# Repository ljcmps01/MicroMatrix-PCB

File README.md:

# MicroMatrix-PCB
PCB for the MicroMatrix project

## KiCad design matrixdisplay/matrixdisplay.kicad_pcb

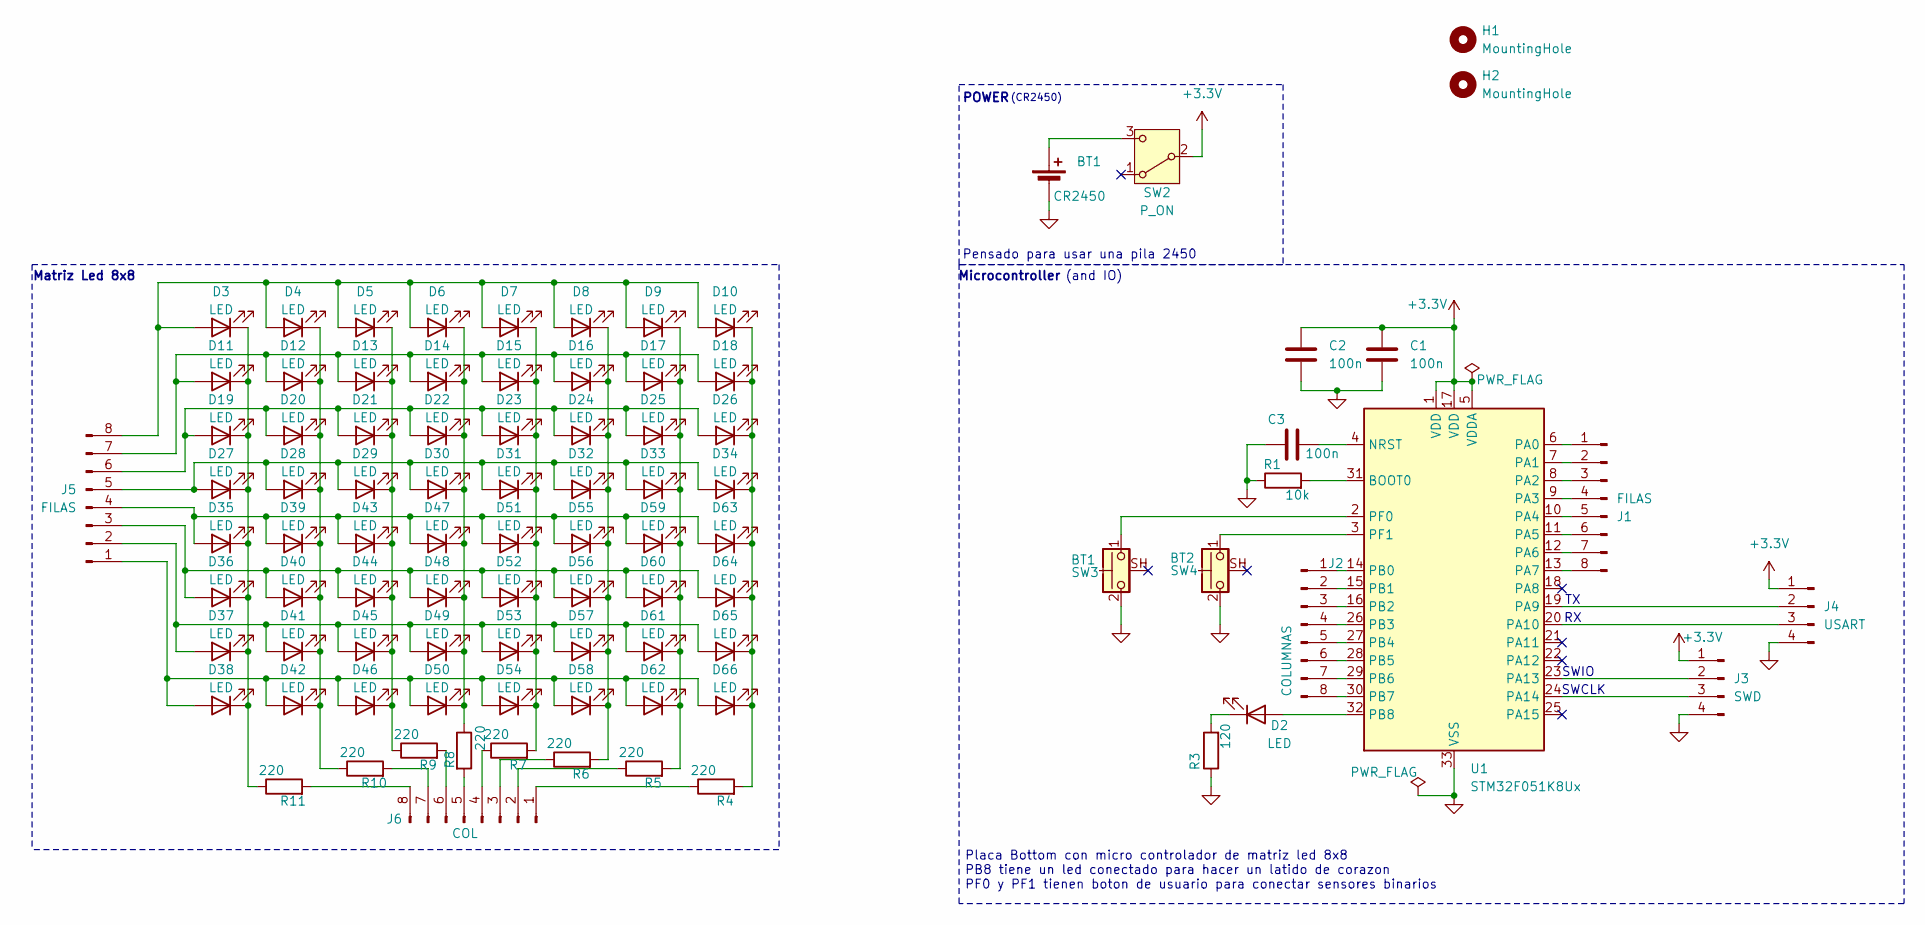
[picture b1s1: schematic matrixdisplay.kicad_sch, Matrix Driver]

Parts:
BT1: CR2450; BatteryHolder_ComfortableElectronic_CH273-2450_1x2450
C1, C2, C3: 100n; C_0603_1608Metric
D2, D3, D4, D5, D6, D7, D8, D9, D10, D11, D12, D13, D14, D15, D16, D17, D18, D19, D20, D21, D22, D23, D24, D25, D26, D27, D28, D29, D30, D31, D32, D33, D34, D35, D36, D37, D38, D39, D40, D41, D42, D43, D44, D45, D46, D47, D48, D49, D50, D51, D52, D53, D54, D55, D56, D57, D58, D59, D60, D61, D62, D63, D64, D65, D66: LED; LED_0603_1608Metric; Manufacturer Part # BL-HJC36G-AV-TRB
H1, H2: MountingHole; MountingHole_2mm
J1: FILAS; PinSocket_1x08_P2.54mm_Vertical
J2: COLUMNAS; PinSocket_1x08_P2.54mm_Vertical
J3: SWD; PinHeader_1x04_P2.54mm_Vertical
J4: USART; PinHeader_1x04_P2.54mm_Vertical
J5: FILAS; PinHeader_1x08_P2.54mm_Vertical
J6: COL; PinHeader_1x08_P2.54mm_Vertical
R1: 10k; R_0603_1608Metric
R3: 120; R_0603_1608Metric
R4, R5, R6, R7, R8, R9, R10, R11: 220; R_0402_1005Metric
SW2: P_ON; SW_SPDT_PCM12; Manufacturer Part # MSK12C02
SW3: BT1; TS24CA; Manufacturer Part # TS24CAC393942
SW4: BT2; TS24CA; Manufacturer Part # TS24CAC393942
U1: STM32F051K8Ux; QFN-32-1EP_5x5mm_P0.5mm_EP3.45x3.45mm

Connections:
+3.3V: C1.1, C2.1, J3.1, J4.1, SW2.2 (B), U1.1 (VDD), U1.5 (VDDA), U1.17 (VDD)
GND: BT1.2 (-), C1.2, C2.2, C3.2, J3.4, J4.4, R1.1, R3.1, SW3.2, SW4.2, U1.33 (VSS); also elsewhere on the board
unnamed 2: BT1.1 (+), SW2.3 (C); also elsewhere on the board
unnamed: D2.2 (A), U1.32 (PB8)
unnamed: D2.1 (K), R3.2
unnamed: D3.2 (A), D4.2 (A), D5.2 (A), D6.2 (A), D7.2 (A), D8.2 (A), D9.2 (A), D10.2 (A), J5.8
unnamed: D10.1 (K), D18.1 (K), D26.1 (K), D34.1 (K), D63.1 (K), D64.1 (K), D65.1 (K), D66.1 (K), R4.2
unnamed: D11.2 (A), D12.2 (A), D13.2 (A), D14.2 (A), D15.2 (A), D16.2 (A), D17.2 (A), D18.2 (A), J5.7
unnamed: D3.1 (K), D11.1 (K), D19.1 (K), D27.1 (K), D35.1 (K), D36.1 (K), D37.1 (K), D38.1 (K), R11.1
unnamed: D4.1 (K), D12.1 (K), D20.1 (K), D28.1 (K), D39.1 (K), D40.1 (K), D41.1 (K), D42.1 (K), R10.1
unnamed: D5.1 (K), D13.1 (K), D21.1 (K), D29.1 (K), D43.1 (K), D44.1 (K), D45.1 (K), D46.1 (K), R9.1
unnamed: D6.1 (K), D14.1 (K), D22.1 (K), D30.1 (K), D47.1 (K), D48.1 (K), D49.1 (K), D50.1 (K), R8.1
unnamed: D7.1 (K), D15.1 (K), D23.1 (K), D31.1 (K), D51.1 (K), D52.1 (K), D53.1 (K), D54.1 (K), R7.2
unnamed: D8.1 (K), D16.1 (K), D24.1 (K), D32.1 (K), D55.1 (K), D56.1 (K), D57.1 (K), D58.1 (K), R6.2
unnamed: D9.1 (K), D17.1 (K), D25.1 (K), D33.1 (K), D59.1 (K), D60.1 (K), D61.1 (K), D62.1 (K), R5.2
unnamed: D19.2 (A), D20.2 (A), D21.2 (A), D22.2 (A), D23.2 (A), D24.2 (A), D25.2 (A), D26.2 (A), J5.6
unnamed: D27.2 (A), D28.2 (A), D29.2 (A), D30.2 (A), D31.2 (A), D32.2 (A), D33.2 (A), D34.2 (A), J5.5
unnamed: D35.2 (A), D39.2 (A), D43.2 (A), D47.2 (A), D51.2 (A), D55.2 (A), D59.2 (A), D63.2 (A), J5.4
unnamed: D36.2 (A), D40.2 (A), D44.2 (A), D48.2 (A), D52.2 (A), D56.2 (A), D60.2 (A), D64.2 (A), J5.3
unnamed: D37.2 (A), D41.2 (A), D45.2 (A), D49.2 (A), D53.2 (A), D57.2 (A), D61.2 (A), D65.2 (A), J5.2
unnamed: D38.2 (A), D42.2 (A), D46.2 (A), D50.2 (A), D54.2 (A), D58.2 (A), D62.2 (A), D66.2 (A), J5.1
unnamed: J1.1, U1.6 (PA0)
unnamed: J1.2, U1.7 (PA1)
unnamed: J1.3, U1.8 (PA2)
unnamed: J1.4, U1.9 (PA3)
unnamed: J1.5, U1.10 (PA4)
unnamed: J1.6, U1.11 (PA5)
unnamed: J1.7, U1.12 (PA6)
unnamed: J1.8, U1.13 (PA7)
unnamed: J2.1, U1.14 (PB0)
unnamed: J2.2, U1.15 (PB1)
unnamed: J2.3, U1.16 (PB2)
unnamed: J2.4, U1.26 (PB3)
unnamed: J2.5, U1.27 (PB4)
unnamed: J2.6, U1.28 (PB5)
unnamed: J2.7, U1.29 (PB6)
unnamed: J2.8, U1.30 (PB7)
unnamed: J3.2, U1.23 (PA13)
unnamed: J3.3, U1.24 (PA14)
unnamed: J4.2, U1.19 (PA9)
unnamed: J4.3, U1.20 (PA10)
unnamed: J6.1, R4.1
unnamed: J6.2, R5.1
unnamed: J6.3, R6.1
unnamed: J6.4, R7.1
unnamed: J6.5, R8.2
unnamed: J6.6, R9.2
unnamed: J6.7, R10.2
unnamed: J6.8, R11.2
unnamed: R1.2, U1.31 (BOOT0)
unnamed: C3.1, U1.4 (NRST)
unnamed: SW3.1, U1.2 (PF0)
unnamed: SW4.1, U1.3 (PF1)

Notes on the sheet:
(CR2450)
Placa Bottom con micro controlador de matriz led 8x8 PB8 tiene un led conectado para hacer un latido de corazon PF0 y PF1 tienen boton de usuario para conectar sensores binarios
SWIO
Microcontroller
(and IO)
Matriz Led 8x8
Pensado para usar una pila 2450
SWCLK
POWER

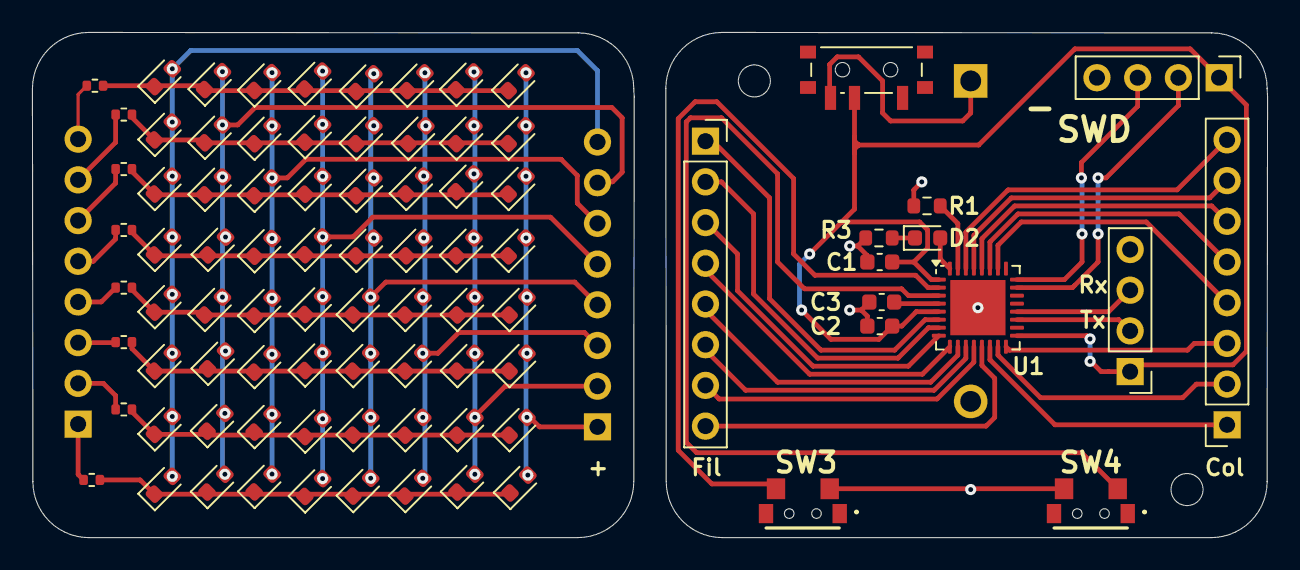
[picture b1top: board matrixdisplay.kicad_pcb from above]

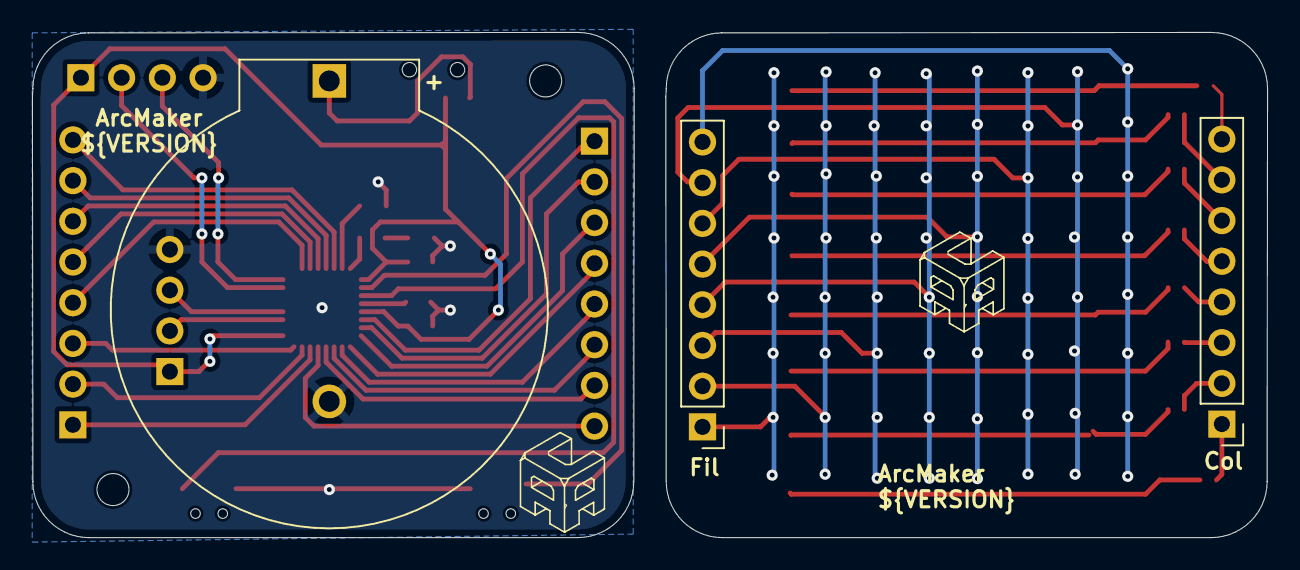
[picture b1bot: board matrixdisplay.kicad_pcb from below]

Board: 2 copper layers, 77.1 x 31.5 mm, 91 parts (3 on the bottom side), 53 nets.

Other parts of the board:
+: CR2450; BatteryHolder_ComfortableElectronic_CH273-2450_1x2450

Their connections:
GND: +.2 (-); also elsewhere on the board
unnamed 2: +.1 (+); also elsewhere on the board

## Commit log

2025-11-13 Add new resource images for board layout and views
    - Added board-layout.png for the overall board design.
    - Added bottom-view.png to provide a view from the bottom.
    - Added isometric-view.png for a 3D perspective of the board.
    - Added top-view.png to show the layout from the top.
2025-11-15 move previews to own version
2025-11-16 Add better ARC logo
2025-11-16 Add automatic labeler script for title block
2025-12-04 feat(scripts): add robust git-based versioning for KiCad projects
    - Adds automated detection and injection of git version, branch, status, and build date into KiCad project text variables
    - Unifies version variable usage in both schematic title blocks and PCB silkscreen
    - Improves CLI UX with dry-run, diagnose, and project-only options
    Enables consistent version tracking and display directly from git history.
2025-12-04 fix(kicad_git_labeler.py): set clean status for unmodified repos
    - Assigns 'clean' status when no uncommitted changes are detected
    - Ensures accurate git status reporting for improved clarity in version labeling
2025-12-05 feat(matrixdisplay): update components to exclude from BOM and save components 3D bodies
2025-12-05 refactor(matrixdisplay.kicad_pro): add title variable for fab files generation
2025-12-05 Add fab files
2025-12-05 update version tag
2025-12-06 Set up project to import EASYEDA models
2025-12-06 feat(power): change battery footprint to match 2450 size
2025-12-06 feat(sch): remove stand by led and update text info
2025-12-08 feat(brd): reroute for CR2450
2025-12-08 Fix (brd): DRC errors
2025-12-08 fix(brd): add cr2450 3d model
